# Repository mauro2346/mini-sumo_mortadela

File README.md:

OK, basicamente este repositorio contiene todo el codigo, pcb y diseño 3D para un robot minisumo de competencias.
La placa fue diseñada con kicad y sus componentes tanto normales como SMD,
un arduino nano, el driver de los motores, las borneras para conectar los mismos y pineras para conectar los sensores infrarrojos como de ultra sonido.
el codigo ya esta listo para correr en un arduino nano con sus pines pmw para los motores y siguiendo todas las reglas del reglamento nacional.
y el diseño 3D esta listo para imprimirse con las medidas exactas 10x10cm, suficiente espacio dentro para colocar los componentes, un techo opcional prar colocar
y un diseño distintivo del pokemon caterpie en pixel art en la parte frontal del mismo

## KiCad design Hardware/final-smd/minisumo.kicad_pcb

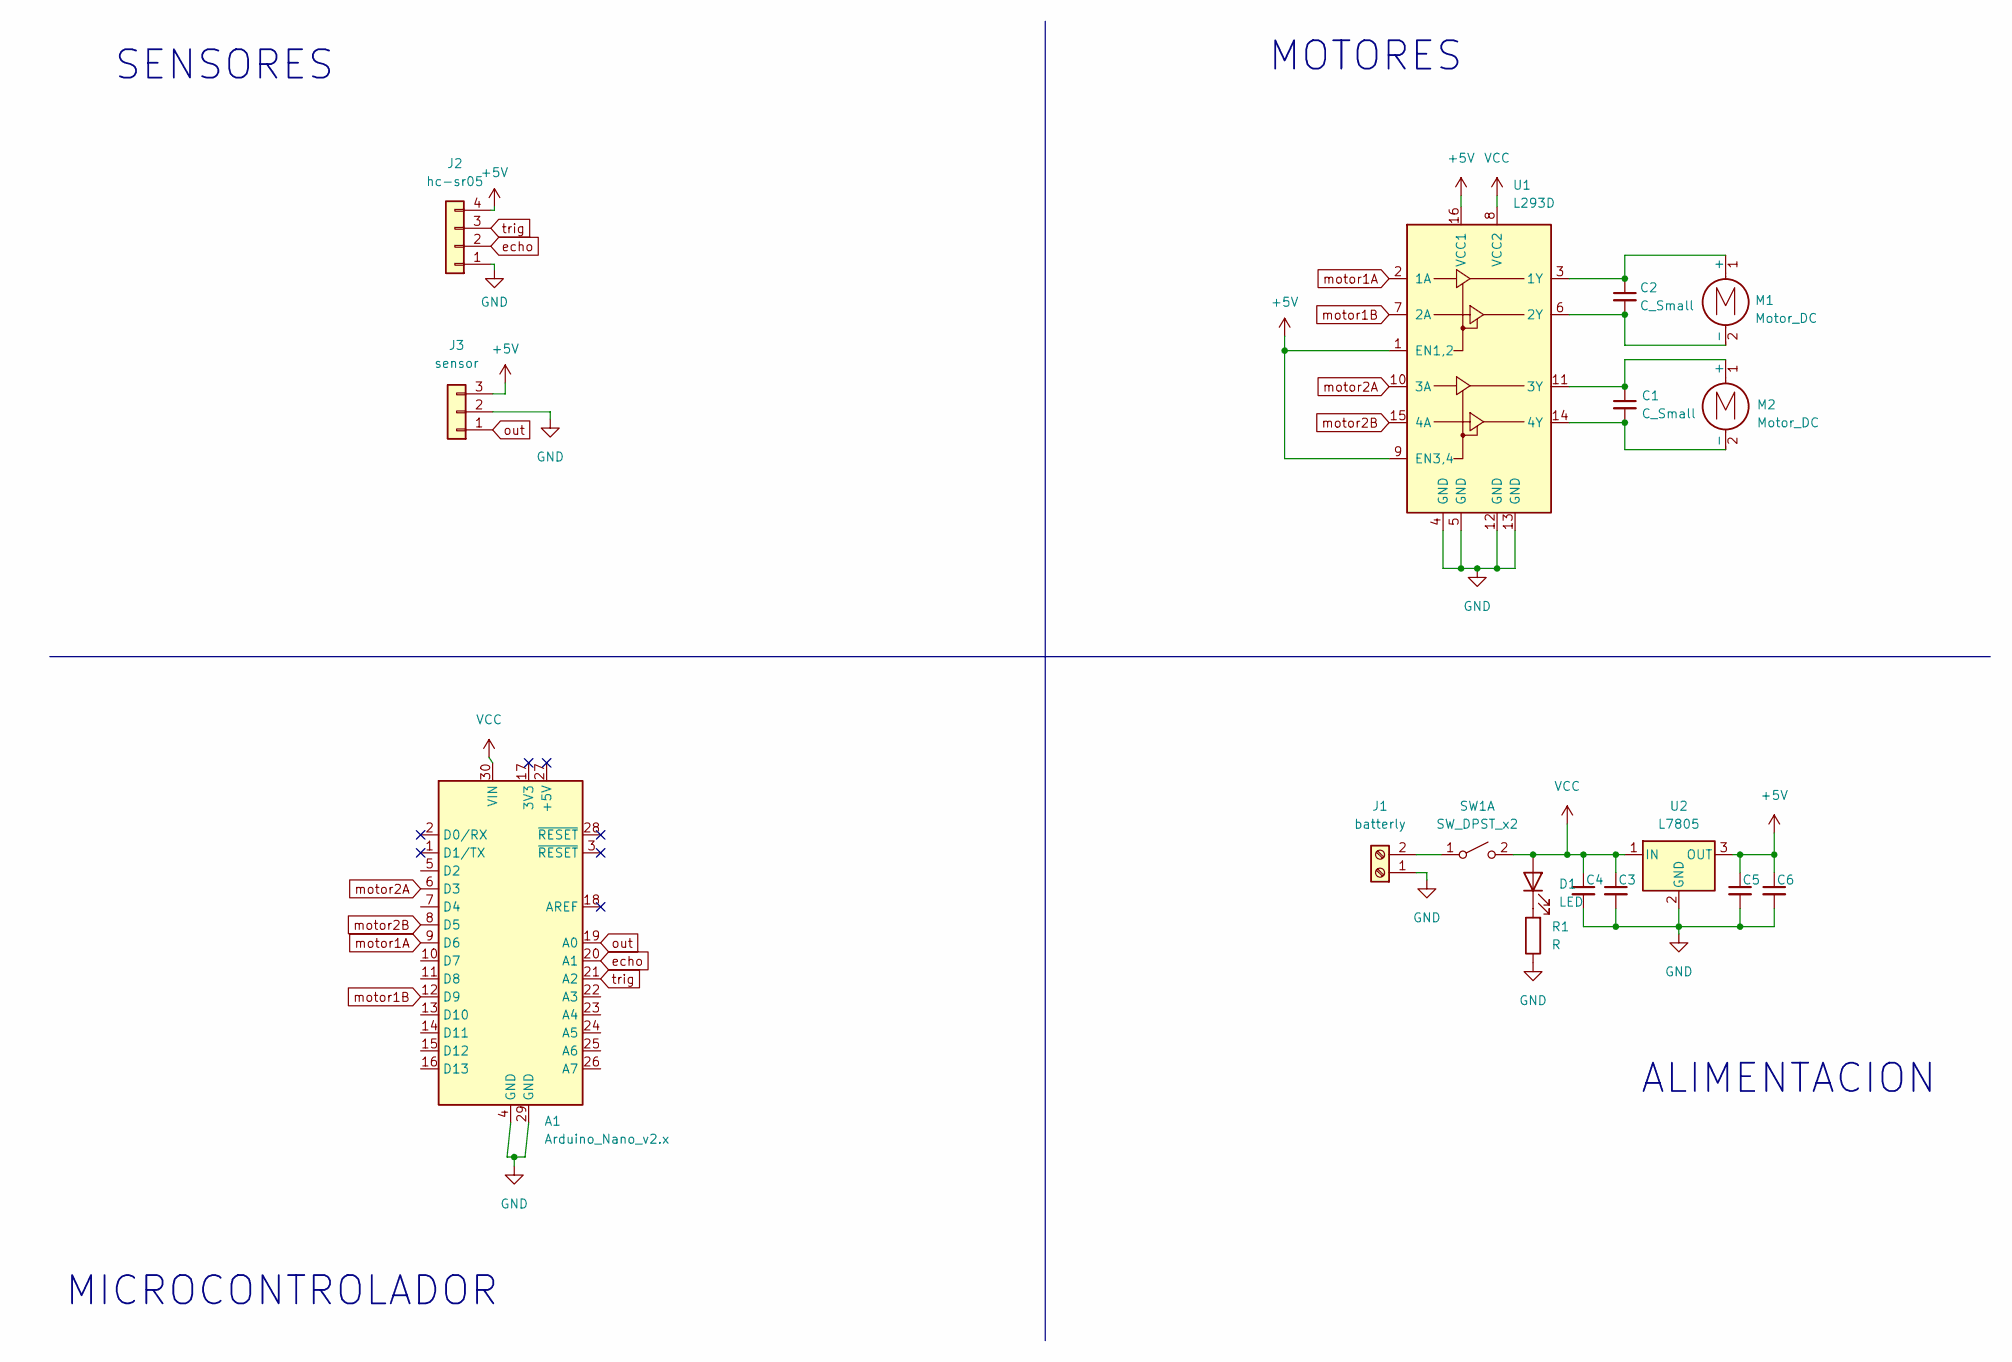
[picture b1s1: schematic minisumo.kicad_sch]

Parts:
A1: Arduino_Nano_v2.x; arduino_nano_header
C1, C2, C3, C4, C5, C6: C_Small; C_0805_2012Metric
D1: LED; led_5mm_red
J1: batterly; BORNERA2_AZUL
J2: hc-sr05; pin_strip_4
J3: sensor; Pin_Header_3
M1, M2: Motor_DC; BORNERA2_AZUL
R1: R; R_0805_2012Metric
SW1: SW_DPST_x2; Cable-doble_THT-switch
U1: L293D; DIP880W50P254L2000H510Q16
U2: L7805; TO-263-3_TabPin2

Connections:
+5V: C5.1, C6.1, J2.4, J3.3, U1.1 (EN1,2), U1.9 (EN3,4), U1.16 (VCC1), U2.3 (OUT)
GND: A1.4 (GND), A1.29 (GND), C3.2, C4.2, C5.2, C6.2, J1.1, J2.1, J3.2, R1.1, U1.4 (GND), U1.5 (GND), U1.12 (GND), U1.13 (GND), U2.2 (GND)
unnamed: D1.1 (K), R1.2
unnamed: J1.2, SW1.1 (A)
unnamed: C2.1, M1.1 (+), U1.3 (1Y)
unnamed: C2.2, M1.2 (-), U1.6 (2Y)
unnamed: C1.1, M2.1 (+), U1.11 (3Y)
unnamed: C1.2, M2.2 (-), U1.14 (4Y)
VCC: A1.30 (VIN), C3.1, C4.1, D1.2 (A), SW1.2 (B), U1.8 (VCC2), U2.1 (IN)
echo: A1.20 (A1), J2.2
motor1A: A1.9 (D6), U1.2 (1A)
motor1B: A1.12 (D9), U1.7 (2A)
motor2A: A1.6 (D3), U1.10 (3A)
motor2B: A1.8 (D5), U1.15 (4A)
out: A1.19 (A0), J3.1
trig: A1.21 (A2), J2.3

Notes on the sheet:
ALIMENTACION
MOTORES
MICROCONTROLADOR
SENSORES

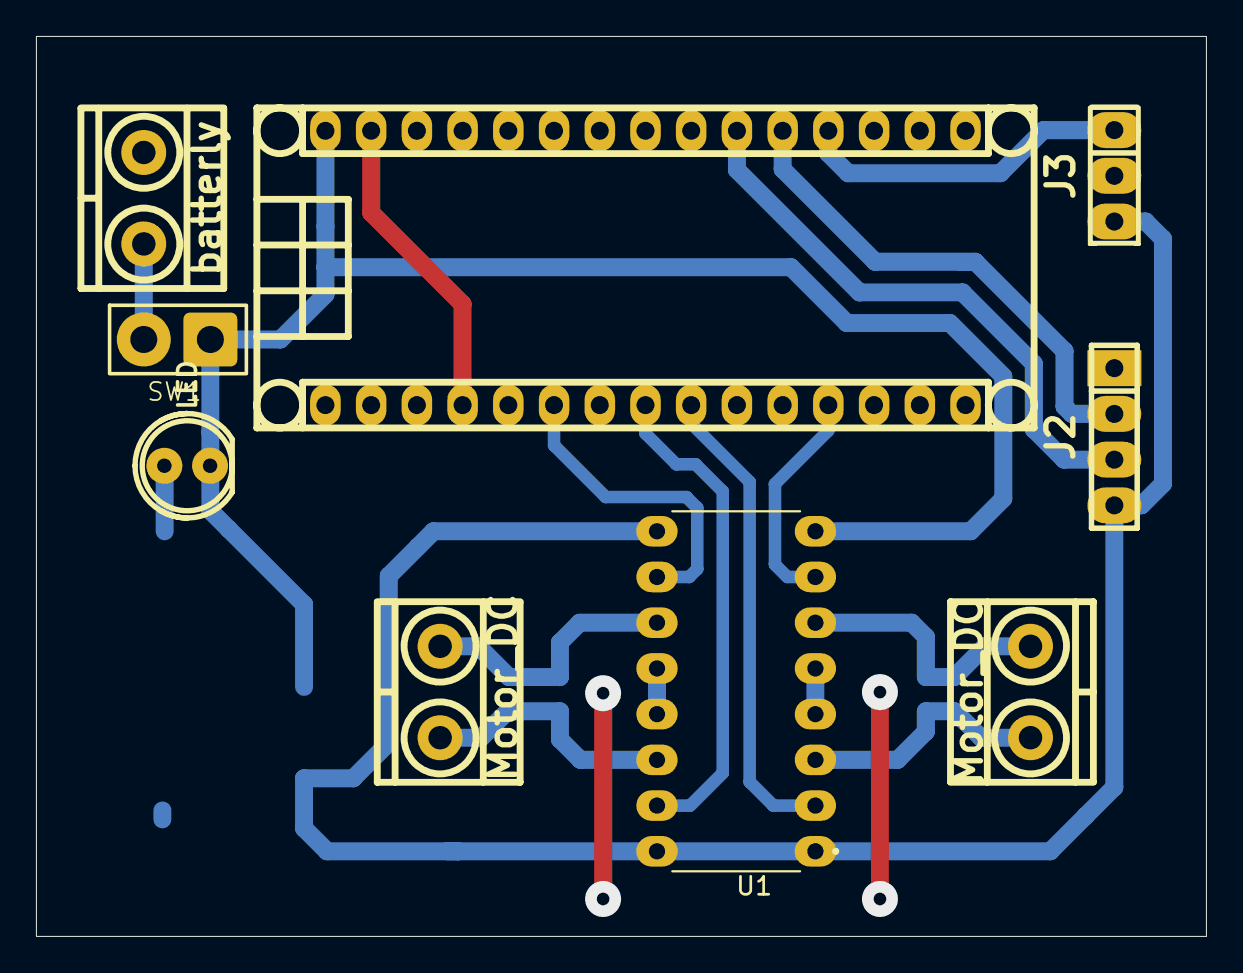
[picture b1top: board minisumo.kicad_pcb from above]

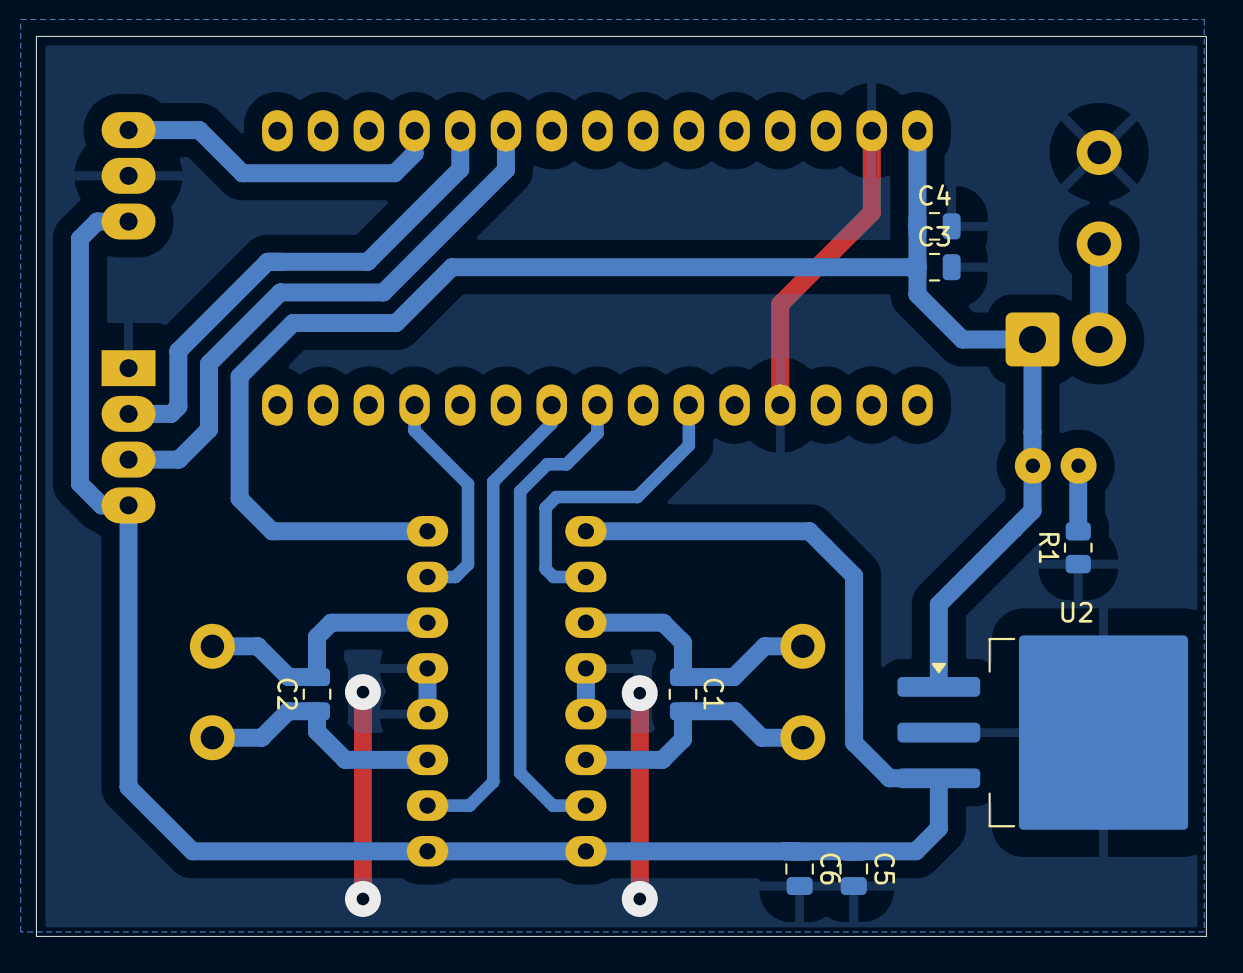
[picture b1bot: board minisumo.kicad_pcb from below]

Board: 2 copper layers, 65.0 x 50.0 mm, 17 parts (8 on the bottom side), 16 nets.

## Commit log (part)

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2026-04-21 commit sumo
2026-04-21 Se agregaron carpetas para el proyecto
2026-06-29 Create Hardware
